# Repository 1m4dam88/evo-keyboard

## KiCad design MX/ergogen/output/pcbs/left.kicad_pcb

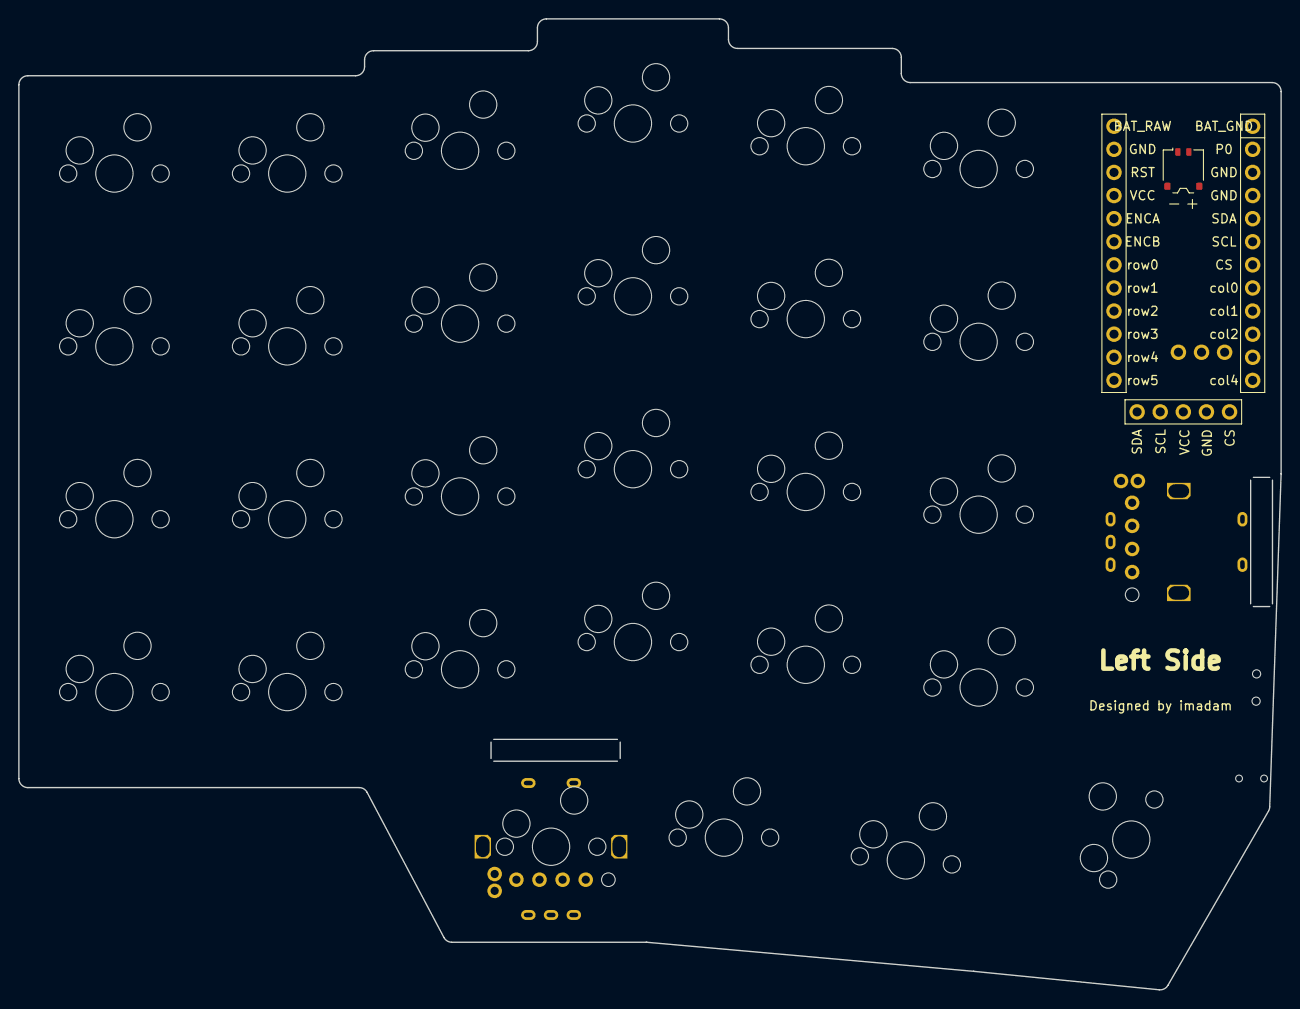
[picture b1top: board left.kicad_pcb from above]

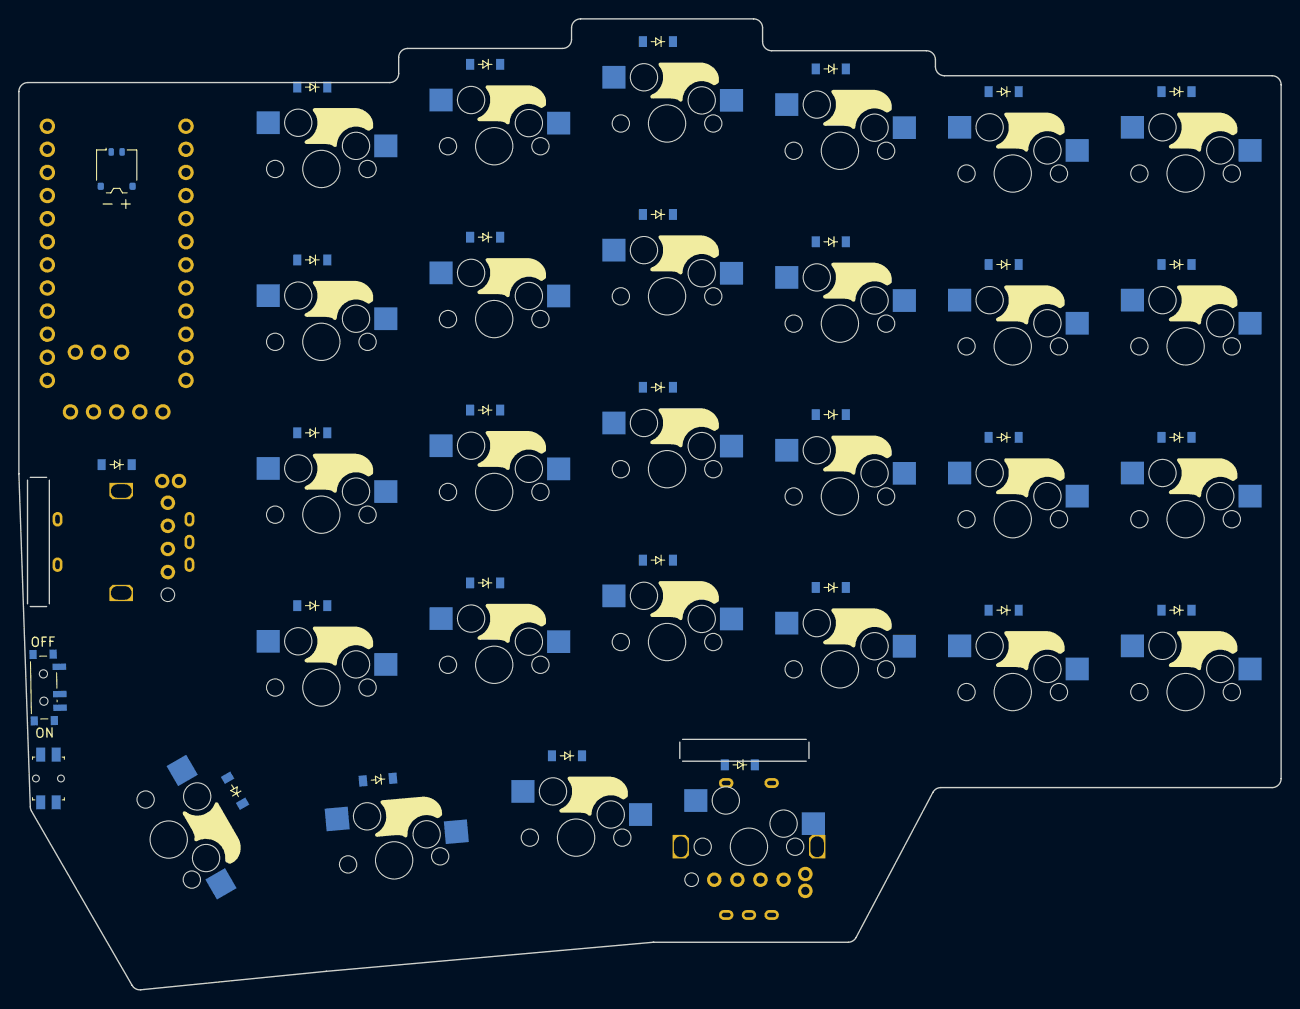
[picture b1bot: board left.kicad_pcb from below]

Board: 2 copper layers, 138.8 x 106.7 mm, 64 parts (59 on the bottom side), 53 nets, no tracks yet.

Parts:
CONN1: battery_connector_molex_pico_ezmate_1x02
D1, D2, D3, D4, D5, D6, D7, D8, D9, D10, D11, D12, D13, D14, D15, D16, D17, D18, D19, D20, D21, D22, D23, D24, D25, D26, D27, D28, D29: diode_tht_sod123
DISP1: display_nice_view
MCU1: mcu_supermini_nrf52840
PWR1: power_switch_smd_side
RE1, RE2: rotary_encoder_ec11_ec12
RST1: reset_switch_smd_side
S1, S2, S3, S4, S5, S6, S7, S8, S9, S10, S11, S12, S13, S14, S15, S16, S17, S18, S19, S20, S21, S22, S23, S24, S25, S26, S27, S28: switch_mx

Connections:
BAT_GND: CONN1.2, MCU1.1
BAT_RAW: MCU1.24, PWR1.2
CS: DISP1.5, MCU1.7
ENCA: MCU1.20, RE1.A
ENCB: MCU1.19, RE1.C
ENCC: MCU1.25, RE2.A
ENCD: MCU1.26, RE2.C
GND: DISP1.4, MCU1.3, MCU1.4, MCU1.23, RE1.B, RE2.B, RST1.2, RST1.4
ON_P: CONN1.1, PWR1.3
RST: MCU1.22, RST1.1, RST1.3
SCL: DISP1.2, MCU1.6
SDA: DISP1.1, MCU1.5
VCC: DISP1.3, MCU1.21
col0: MCU1.8, S1.1, S2.1, S3.1, S4.1
col1: MCU1.9, S5.1, S6.1, S7.1, S8.1
col2: MCU1.10, RE2.S1, S9.1, S10.1, S11.1, S12.1, S28.1
col3: MCU1.11, S13.1, S14.1, S15.1, S16.1, S25.1
col4: MCU1.12, S17.1, S18.1, S19.1, S20.1, S26.1
col5: RE1.S1, S21.1, S22.1, S23.1, S24.1, S27.1
home_cluster: D26.2, S25.2
index_bottom: D17.2, S17.2
index_home: D18.2, S18.2
index_num: D20.2, S20.2
index_top: D19.2, S19.2
inner_bottom: D21.2, S21.2
inner_cluster: D25.2, RE2.S2, S28.2
inner_home: D22.2, S22.2
inner_num: D24.2, S24.2
inner_top: D23.2, S23.2
layer_cluster: D27.2, S26.2
middle_bottom: D13.2, S13.2
middle_home: D14.2, S14.2
middle_num: D16.2, S16.2
middle_top: D15.2, S15.2
outer_bottom: D1.2, S1.2
outer_home: D2.2, S2.2
outer_num: D4.2, S4.2
outer_top: D3.2, S3.2
pinky_bottom: D5.2, S5.2
pinky_home: D6.2, S6.2
pinky_num: D8.2, S8.2
pinky_top: D7.2, S7.2
ring_bottom: D9.2, S9.2
ring_home: D10.2, S10.2
ring_num: D12.2, S12.2
ring_top: D11.2, S11.2
row0: D4.1, D8.1, D12.1, D16.1, D20.1, D24.1, MCU1.18
row1: D3.1, D7.1, D11.1, D15.1, D19.1, D23.1, MCU1.17
row2: D2.1, D6.1, D10.1, D14.1, D18.1, D22.1, D29.1, MCU1.16
row3: D1.1, D5.1, D9.1, D13.1, D17.1, D21.1, MCU1.15
row4: D25.1, D26.1, D27.1, D28.1, MCU1.14
scrollwheel_enc: D29.2, RE1.S2
space_cluster: D28.2, S27.2
